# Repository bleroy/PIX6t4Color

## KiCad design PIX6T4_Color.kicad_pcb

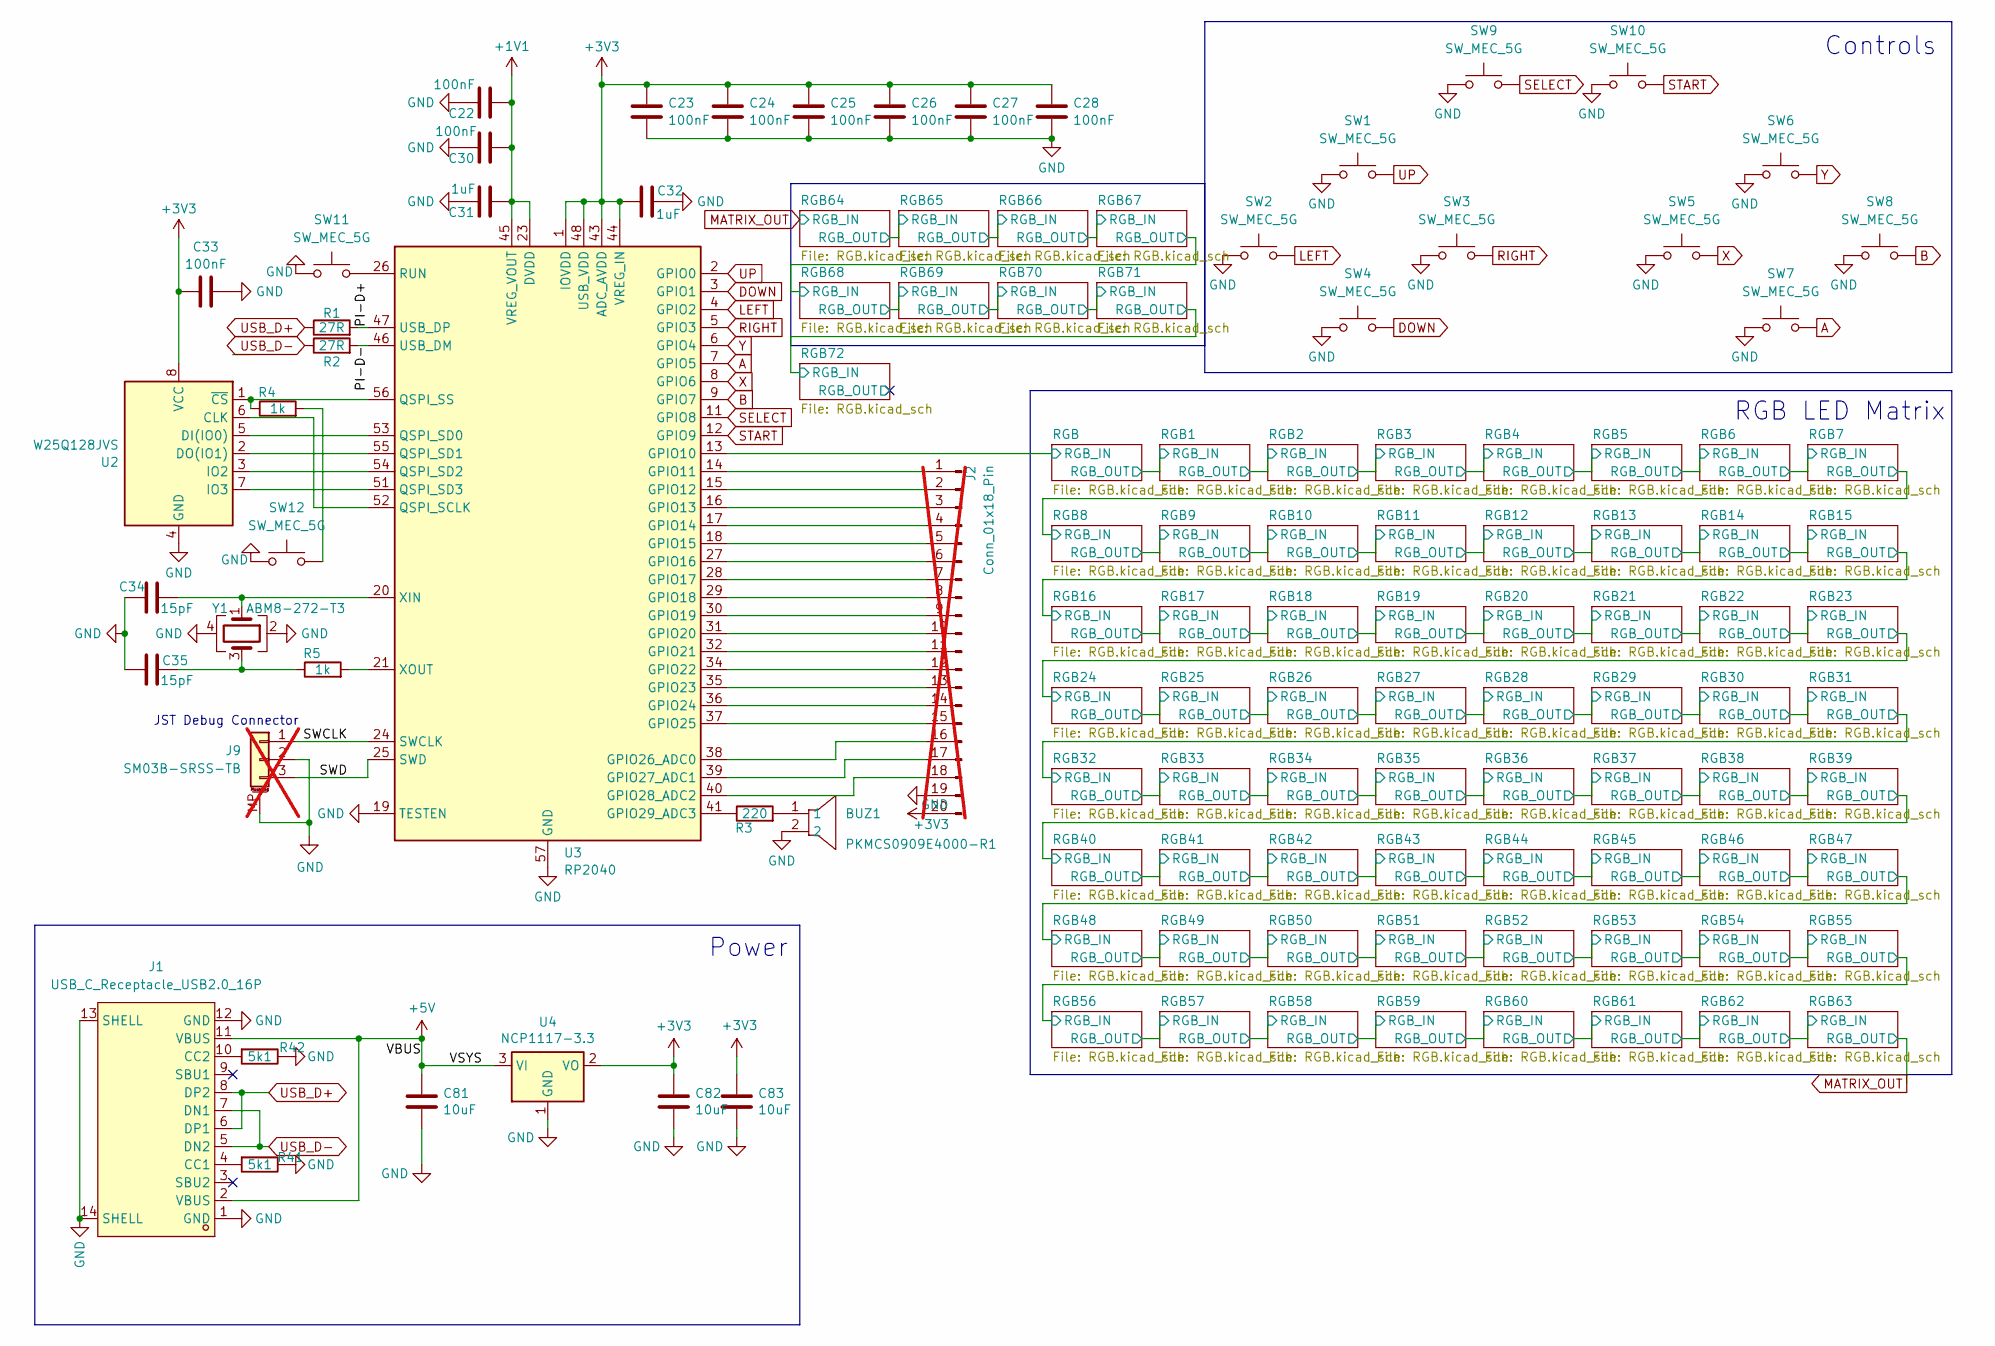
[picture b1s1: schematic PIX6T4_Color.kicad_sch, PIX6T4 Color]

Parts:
BUZ1: PKMCS0909E4000-R1; BUZ-SMD_L9.0-W9.0_PKMCS0909E4000-R1; JLCPCB Part # C910763
C22, C23, C24, C25, C26, C27, C28, C30, C33: 100nF; C_0402_1005Metric; JLCPCB Part # C1525
C31, C32: 1uF; C_0402_1005Metric; JLCPCB Part # C52923
C34, C35: 15pF; C_0402_1005Metric; JLCPCB Part # C1548
C81, C82, C83: 10uF; C_0402_1005Metric; JLCPCB Part # C15525
J1: USB_C_Receptacle_USB2.0_16P; USB-C-SMD_TYPE-C-6PIN-2MD-073; JLCPCB Part # C2765186
J2: Conn_01x18_Pin; PinHeader_1x20_P2.54mm_Vertical; not fitted
J9: SM03B-SRSS-TB; JST_SH_SM03B-SRSS-TB_1x03-1MP_P1.00mm_Horizontal; JLCPCB Part # C160389; not fitted
R1, R2: 27R; R_0805_2012Metric; JLCPCB Part # C17561
R3: 220; R_0402_1005Metric; JLCPCB Part # C25091
R4, R5: 1k; R_0402_1005Metric; JLCPCB Part # C11702
R41, R42: 5k1; R_0402_1005Metric; JLCPCB Part # C25905
SW1, SW2, SW3, SW4, SW5, SW6, SW7, SW8, SW9, SW10: SW_MEC_5G; SW-SMD_4P-L5.1-W5.1-P3.70-LS6.5-TL_H1.5; JLCPCB Part # C318884
SW11, SW12: SW_MEC_5G; SW-SMD_2P-TS24CA; JLCPCB Part # C393942
U2: W25Q128JVS; SOIC-8_L5.3-W5.3-P1.27-LS8.0-BL; JLCPCB Part # C97521
U3: RP2040; QFN-56-1EP_7x7mm_P0.4mm_EP3.2x3.2mm; JLCPCB Part # C2040
U4: NCP1117-3.3; SOT-223-3_TabPin2; JLCPCB Part # C6186
Y1: ABM8-272-T3; Oscillator_SMD_Abracon_ASE-4Pin_3.2x2.5mm; JLCPCB Part # C20625731

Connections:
+1V1: C22.1, C30.1, C31.1, U3.23 (DVDD), U3.45 (VREG_VOUT), U3.50 (DVDD)
+3V3: C23.1, C24.1, C25.1, C26.1, C27.1, C28.1, C32.1, C33.2, C82.1, C83.1, J2.20, U2.8 (VCC), U3.1 (IOVDD), U3.10 (IOVDD), U3.22 (IOVDD), U3.33 (IOVDD), U3.42 (IOVDD), U3.43 (ADC_AVDD), U3.44 (VREG_IN), U3.48 (USB_VDD), U3.49 (IOVDD), U4.2 (VO)
+5V: C81.1, J1.2 (VBUS), J1.11 (VBUS), U4.3 (VI); also elsewhere on the board
/PI-D+: R1.2, U3.47 (USB_DP)
/PI-D-: R2.2, U3.46 (USB_DM)
/RGB/RGB_IN: U3.13 (GPIO10); also elsewhere on the board
/SWCLK: J9.1, U3.24 (SWCLK)
/SWD: J9.3, U3.25 (SWD)
A: SW7.3 (B), SW7.4 (B), U3.7 (GPIO5)
B: SW8.3 (B), SW8.4 (B), U3.9 (GPIO7)
DOWN: SW4.3 (B), SW4.4 (B), U3.3 (GPIO1)
GND: BUZ1.2, C22.2, C23.2, C24.2, C25.2, C26.2, C27.2, C28.2, C30.2, C31.2, C32.2, C33.1, C34.1, C35.1, C81.2, C82.2, C83.2, J1.1 (GND), J1.12 (GND), J1.13 (SHELL), J1.14 (SHELL), J2.19, J9.2, J9.MP (MountPin), R41.1, R42.1, SW1.1 (A), SW1.2 (A), SW2.1 (A), SW2.2 (A), SW3.1 (A), SW3.2 (A), SW4.1 (A), SW4.2 (A), SW5.1 (A), SW5.2 (A), SW6.1 (A), SW6.2 (A), SW7.1 (A), SW7.2 (A), SW8.1 (A), SW8.2 (A), SW9.1 (A), SW9.2 (A), SW10.1 (A), SW10.2 (A), SW11.1 (A), SW11.2 (A), SW12.1 (A), SW12.2 (A), U2.4 (GND), U3.19 (TESTEN), U3.57 (GND), U4.1 (GND), Y1.2, Y1.4; also elsewhere on the board
LEFT: SW2.3 (B), SW2.4 (B), U3.4 (GPIO2)
unnamed: BUZ1.1, R3.2
unnamed: C35.2, R5.1, Y1.3
unnamed: J1.4 (CC1), R41.2
unnamed: J1.10 (CC2), R42.2
unnamed: J2.1, U3.14 (GPIO11)
unnamed: J2.2, U3.15 (GPIO12)
unnamed: J2.3, U3.16 (GPIO13)
unnamed: J2.4, U3.17 (GPIO14)
unnamed: J2.5, U3.18 (GPIO15)
unnamed: J2.6, U3.27 (GPIO16)
unnamed: J2.7, U3.28 (GPIO17)
unnamed: J2.8, U3.29 (GPIO18)
unnamed: J2.9, U3.30 (GPIO19)
unnamed: J2.10, U3.31 (GPIO20)
unnamed: J2.11, U3.32 (GPIO21)
unnamed: J2.12, U3.34 (GPIO22)
unnamed: J2.13, U3.35 (GPIO23)
unnamed: J2.14, U3.36 (GPIO24)
unnamed: J2.15, U3.37 (GPIO25)
unnamed: J2.16, U3.38 (GPIO26_ADC0)
unnamed: J2.17, U3.39 (GPIO27_ADC1)
unnamed: J2.18, U3.40 (GPIO28_ADC2)
unnamed: R4.2, SW12.3 (B), SW12.4 (B)
unnamed: U2.6 (CLK), U3.52 (QSPI_SCLK)
unnamed: U2.5 (DI(IO0)), U3.53 (QSPI_SD0)
unnamed: U2.2 (DO(IO1)), U3.55 (QSPI_SD1)
unnamed: U2.3 (IO2), U3.54 (QSPI_SD2)
unnamed: U2.7 (IO3), U3.51 (QSPI_SD3)
unnamed: R4.1, U2.1 (~CS), U3.56 (QSPI_SS)
unnamed: R3.1, U3.41 (GPIO29_ADC3)
unnamed: SW11.3 (B), SW11.4 (B), U3.26 (RUN)
unnamed: C34.2, U3.20 (XIN), Y1.1
unnamed: R5.2, U3.21 (XOUT)
RIGHT: SW3.3 (B), SW3.4 (B), U3.5 (GPIO3)
SELECT: SW9.3 (B), SW9.4 (B), U3.11 (GPIO8)
START: SW10.3 (B), SW10.4 (B), U3.12 (GPIO9)
UP: SW1.3 (B), SW1.4 (B), U3.2 (GPIO0)
USB_D+: J1.6 (DP1), J1.8 (DP2), R1.1
USB_D-: J1.5 (DN2), J1.7 (DN1), R2.1
X: SW5.3 (B), SW5.4 (B), U3.8 (GPIO6)
Y: SW6.3 (B), SW6.4 (B), U3.6 (GPIO4)

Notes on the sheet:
JST Debug Connector
Power
RGB LED Matrix
Controls

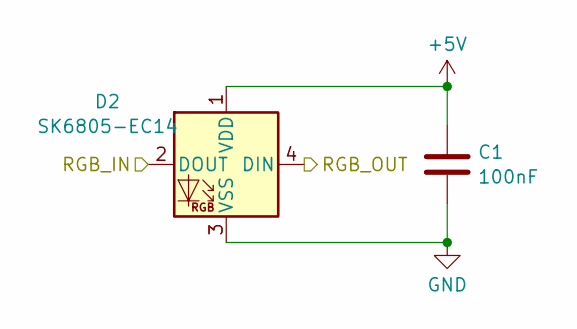
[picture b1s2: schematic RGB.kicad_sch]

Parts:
C1: 100nF; C_0402_1005Metric; JLCPCB Part # C1525
D2: SK6805-EC14; LED-SMD_4P-L1.4-W1.4-TL; JLCPCB Part # C2909055

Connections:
+5V: C1.1, D2.1 (VDD); also elsewhere on the board
/RGB/RGB_IN: D2.4 (DIN); also elsewhere on the board
/RGB/RGB_OUT: D2.2 (DOUT); also elsewhere on the board
GND: C1.2, D2.3 (VSS); also elsewhere on the board

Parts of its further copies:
C2, C3, C4, C5, C6, C7, C8, C9, C10, C11, C12, C13, C14, C15, C16, C17, C18, C19, C20, C21, C29, C36, C37, C38, C39, C40, C41, C42, C43, C44, C45, C46, C47, C48, C49, C50, C51, C52, C53, C54, C55, C56, C57, C58, C59, C60, C61, C62, C63, C64, C65, C66, C67, C68, C69, C70, C71, C72, C73, C74, C75, C76, C77, C78, C79, C80, C84, C85, C86, C87, C88, C89: 100nF; C_0402_1005Metric; JLCPCB Part # C1525
D1, D3, D4, D5, D6, D7, D8, D9, D10, D11, D12, D13, D14, D15, D16, D17, D18, D19, D20, D21, D22, D23, D24, D25, D26, D27, D28, D29, D30, D31, D32, D33, D34, D35, D36, D37, D38, D39, D40, D41, D42, D43, D44, D45, D46, D47, D48, D49, D50, D51, D52, D53, D54, D55, D56, D57, D58, D59, D60, D61, D62, D63, D64, D65, D66, D67, D68, D69, D70, D71, D72, D73: SK6805-EC14; LED-SMD_4P-L1.4-W1.4-TL; JLCPCB Part # C2909055

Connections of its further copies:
+5V: C2.1, C3.1, C4.1, C5.1, C6.1, C7.1, C8.1, C9.1, C10.1, C11.1, C12.1, C13.1, C14.1, C15.1, C16.1, C17.1, C18.1, C19.1, C20.1, C21.1, C29.1, C36.1, C37.1, C38.1, C39.1, C40.1, C41.1, C42.1, C43.1, C44.1, C45.1, C46.1, C47.1, C48.1, C49.1, C50.1, C51.1, C52.1, C53.1, C54.1, C55.1, C56.1, C57.1, C58.1, C59.1, C60.1, C61.1, C62.1, C63.1, C64.1, C65.1, C66.1, C67.1, C68.1, C69.1, C70.1, C71.1, C72.1, C73.1, C74.1, C75.1, C76.1, C77.1, C78.1, C79.1, C80.1, C84.1, C85.1, C86.1, C87.1, C88.1, C89.1, D1.1 (VDD), D3.1 (VDD), D4.1 (VDD), D5.1 (VDD), D6.1 (VDD), D7.1 (VDD), D8.1 (VDD), D9.1 (VDD), D10.1 (VDD), D11.1 (VDD), D12.1 (VDD), D13.1 (VDD), D14.1 (VDD), D15.1 (VDD), D16.1 (VDD), D17.1 (VDD), D18.1 (VDD), D19.1 (VDD), D20.1 (VDD), D21.1 (VDD), D22.1 (VDD), D23.1 (VDD), D24.1 (VDD), D25.1 (VDD), D26.1 (VDD), D27.1 (VDD), D28.1 (VDD), D29.1 (VDD), D30.1 (VDD), D31.1 (VDD), D32.1 (VDD), D33.1 (VDD), D34.1 (VDD), D35.1 (VDD), D36.1 (VDD), D37.1 (VDD), D38.1 (VDD), D39.1 (VDD), D40.1 (VDD), D41.1 (VDD), D42.1 (VDD), D43.1 (VDD), D44.1 (VDD), D45.1 (VDD), D46.1 (VDD), D47.1 (VDD), D48.1 (VDD), D49.1 (VDD), D50.1 (VDD), D51.1 (VDD), D52.1 (VDD), D53.1 (VDD), D54.1 (VDD), D55.1 (VDD), D56.1 (VDD), D57.1 (VDD), D58.1 (VDD), D59.1 (VDD), D60.1 (VDD), D61.1 (VDD), D62.1 (VDD), D63.1 (VDD), D64.1 (VDD), D65.1 (VDD), D66.1 (VDD), D67.1 (VDD), D68.1 (VDD), D69.1 (VDD), D70.1 (VDD), D71.1 (VDD), D72.1 (VDD), D73.1 (VDD); also elsewhere on the board
/RGB1/RGB_OUT: D1.2 (DOUT), D3.4 (DIN)
/RGB2/RGB_OUT: D3.2 (DOUT), D4.4 (DIN)
/RGB3/RGB_OUT: D4.2 (DOUT), D5.4 (DIN)
/RGB4/RGB_OUT: D5.2 (DOUT), D6.4 (DIN)
/RGB5/RGB_OUT: D6.2 (DOUT), D7.4 (DIN)
/RGB6/RGB_OUT: D7.2 (DOUT), D8.4 (DIN)
/RGB7/RGB_OUT: D8.2 (DOUT), D9.4 (DIN)
/RGB8/RGB_OUT: D9.2 (DOUT), D10.4 (DIN)
/RGB10/RGB_IN: D10.2 (DOUT), D11.4 (DIN)
/RGB10/RGB_OUT: D11.2 (DOUT), D12.4 (DIN)
/RGB11/RGB_OUT: D12.2 (DOUT), D13.4 (DIN)
/RGB12/RGB_OUT: D13.2 (DOUT), D14.4 (DIN)
/RGB13/RGB_OUT: D14.2 (DOUT), D15.4 (DIN)
/RGB14/RGB_OUT: D15.2 (DOUT), D16.4 (DIN)
/RGB15/RGB_OUT: D16.2 (DOUT), D17.4 (DIN)
/RGB16/RGB_OUT: D17.2 (DOUT), D18.4 (DIN)
/RGB17/RGB_OUT: D18.2 (DOUT), D19.4 (DIN)
/RGB18/RGB_OUT: D19.2 (DOUT), D20.4 (DIN)
/RGB19/RGB_OUT: D20.2 (DOUT), D21.4 (DIN)
/RGB20/RGB_OUT: D21.2 (DOUT), D22.4 (DIN)
/RGB21/RGB_OUT: D22.2 (DOUT), D23.4 (DIN)
/RGB22/RGB_OUT: D23.2 (DOUT), D24.4 (DIN)
/RGB23/RGB_OUT: D24.2 (DOUT), D25.4 (DIN)
/RGB24/RGB_OUT: D25.2 (DOUT), D26.4 (DIN)
/RGB25/RGB_OUT: D26.2 (DOUT), D27.4 (DIN)
/RGB26/RGB_OUT: D27.2 (DOUT), D28.4 (DIN)
/RGB27/RGB_OUT: D28.2 (DOUT), D29.4 (DIN)
/RGB28/RGB_OUT: D29.2 (DOUT), D30.4 (DIN)
/RGB29/RGB_OUT: D30.2 (DOUT), D31.4 (DIN)
/RGB30/RGB_OUT: D31.2 (DOUT), D32.4 (DIN)
/RGB31/RGB_OUT: D32.2 (DOUT), D33.4 (DIN)
/RGB32/RGB_OUT: D33.2 (DOUT), D34.4 (DIN)
/RGB33/RGB_OUT: D34.2 (DOUT), D35.4 (DIN)
/RGB34/RGB_OUT: D35.2 (DOUT), D36.4 (DIN)
/RGB35/RGB_OUT: D36.2 (DOUT), D37.4 (DIN)
/RGB36/RGB_OUT: D37.2 (DOUT), D38.4 (DIN)
/RGB37/RGB_OUT: D38.2 (DOUT), D39.4 (DIN)
/RGB38/RGB_OUT: D39.2 (DOUT), D40.4 (DIN)
/RGB39/RGB_OUT: D40.2 (DOUT), D41.4 (DIN)
/RGB40/RGB_OUT: D41.2 (DOUT), D42.4 (DIN)
/RGB41/RGB_OUT: D42.2 (DOUT), D43.4 (DIN)
/RGB42/RGB_OUT: D43.2 (DOUT), D44.4 (DIN)
/RGB43/RGB_OUT: D44.2 (DOUT), D45.4 (DIN)
/RGB44/RGB_OUT: D45.2 (DOUT), D46.4 (DIN)
/RGB45/RGB_OUT: D46.2 (DOUT), D47.4 (DIN)
/RGB46/RGB_OUT: D47.2 (DOUT), D48.4 (DIN)
/RGB47/RGB_OUT: D48.2 (DOUT), D49.4 (DIN)
/RGB48/RGB_OUT: D49.2 (DOUT), D50.4 (DIN)
/RGB49/RGB_OUT: D50.2 (DOUT), D51.4 (DIN)
/RGB50/RGB_OUT: D51.2 (DOUT), D52.4 (DIN)
/RGB51/RGB_OUT: D52.2 (DOUT), D53.4 (DIN)
/RGB52/RGB_OUT: D53.2 (DOUT), D54.4 (DIN)
/RGB53/RGB_OUT: D54.2 (DOUT), D55.4 (DIN)
/RGB54/RGB_OUT: D55.2 (DOUT), D56.4 (DIN)
/RGB55/RGB_OUT: D56.2 (DOUT), D57.4 (DIN)
/RGB56/RGB_OUT: D57.2 (DOUT), D58.4 (DIN)
/RGB57/RGB_OUT: D58.2 (DOUT), D59.4 (DIN)
/RGB58/RGB_OUT: D59.2 (DOUT), D60.4 (DIN)
/RGB59/RGB_OUT: D60.2 (DOUT), D61.4 (DIN)
/RGB60/RGB_OUT: D61.2 (DOUT), D62.4 (DIN)
/RGB61/RGB_OUT: D62.2 (DOUT), D63.4 (DIN)
/RGB62/RGB_OUT: D63.2 (DOUT), D64.4 (DIN)
/RGB64/RGB_OUT: D65.2 (DOUT), D66.4 (DIN)
/RGB65/RGB_OUT: D66.2 (DOUT), D67.4 (DIN)
/RGB66/RGB_OUT: D67.2 (DOUT), D68.4 (DIN)
/RGB67/RGB_OUT: D68.2 (DOUT), D69.4 (DIN)
/RGB68/RGB_OUT: D69.2 (DOUT), D70.4 (DIN)
/RGB69/RGB_OUT: D70.2 (DOUT), D71.4 (DIN)
/RGB70/RGB_OUT: D71.2 (DOUT), D72.4 (DIN)
/RGB71/RGB_OUT: D72.2 (DOUT), D73.4 (DIN)
/RGB72/RGB_OUT: D73.2 (DOUT)
/RGB/RGB_OUT: D1.4 (DIN); also elsewhere on the board
GND: C2.2, C3.2, C4.2, C5.2, C6.2, C7.2, C8.2, C9.2, C10.2, C11.2, C12.2, C13.2, C14.2, C15.2, C16.2, C17.2, C18.2, C19.2, C20.2, C21.2, C29.2, C36.2, C37.2, C38.2, C39.2, C40.2, C41.2, C42.2, C43.2, C44.2, C45.2, C46.2, C47.2, C48.2, C49.2, C50.2, C51.2, C52.2, C53.2, C54.2, C55.2, C56.2, C57.2, C58.2, C59.2, C60.2, C61.2, C62.2, C63.2, C64.2, C65.2, C66.2, C67.2, C68.2, C69.2, C70.2, C71.2, C72.2, C73.2, C74.2, C75.2, C76.2, C77.2, C78.2, C79.2, C80.2, C84.2, C85.2, C86.2, C87.2, C88.2, C89.2, D1.3 (VSS), D3.3 (VSS), D4.3 (VSS), D5.3 (VSS), D6.3 (VSS), D7.3 (VSS), D8.3 (VSS), D9.3 (VSS), D10.3 (VSS), D11.3 (VSS), D12.3 (VSS), D13.3 (VSS), D14.3 (VSS), D15.3 (VSS), D16.3 (VSS), D17.3 (VSS), D18.3 (VSS), D19.3 (VSS), D20.3 (VSS), D21.3 (VSS), D22.3 (VSS), D23.3 (VSS), D24.3 (VSS), D25.3 (VSS), D26.3 (VSS), D27.3 (VSS), D28.3 (VSS), D29.3 (VSS), D30.3 (VSS), D31.3 (VSS), D32.3 (VSS), D33.3 (VSS), D34.3 (VSS), D35.3 (VSS), D36.3 (VSS), D37.3 (VSS), D38.3 (VSS), D39.3 (VSS), D40.3 (VSS), D41.3 (VSS), D42.3 (VSS), D43.3 (VSS), D44.3 (VSS), D45.3 (VSS), D46.3 (VSS), D47.3 (VSS), D48.3 (VSS), D49.3 (VSS), D50.3 (VSS), D51.3 (VSS), D52.3 (VSS), D53.3 (VSS), D54.3 (VSS), D55.3 (VSS), D56.3 (VSS), D57.3 (VSS), D58.3 (VSS), D59.3 (VSS), D60.3 (VSS), D61.3 (VSS), D62.3 (VSS), D63.3 (VSS), D64.3 (VSS), D65.3 (VSS), D66.3 (VSS), D67.3 (VSS), D68.3 (VSS), D69.3 (VSS), D70.3 (VSS), D71.3 (VSS), D72.3 (VSS), D73.3 (VSS); also elsewhere on the board
MATRIX_OUT: D64.2 (DOUT), D65.4 (DIN)

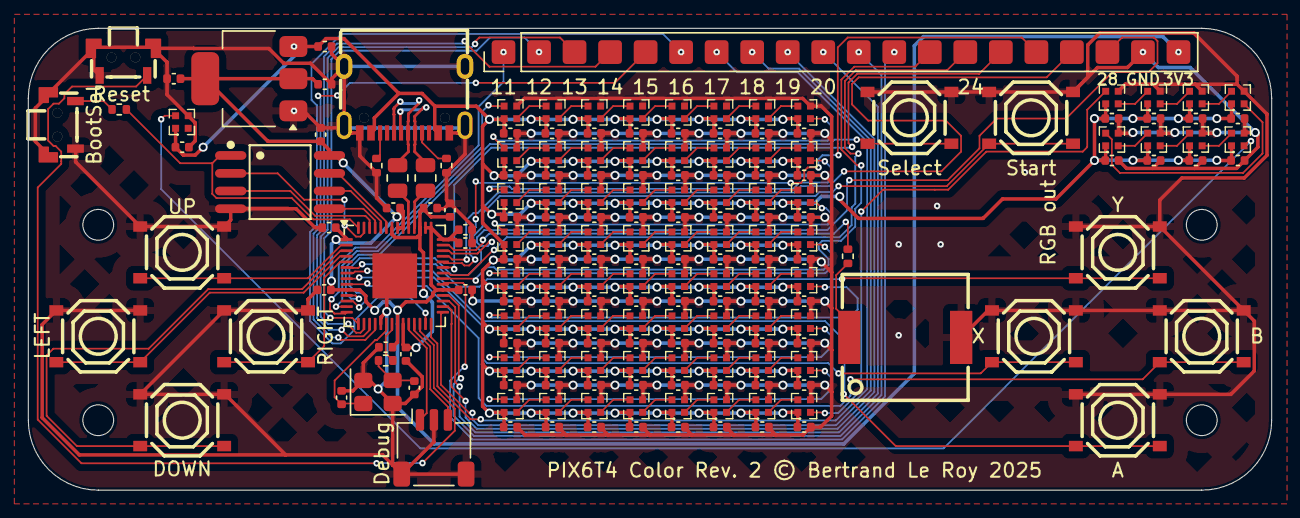
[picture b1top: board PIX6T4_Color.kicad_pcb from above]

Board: 2 copper layers, 88.9 x 33.0 mm, 189 parts (0 on the bottom side), 126 nets.

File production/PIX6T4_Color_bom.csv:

Designator,Footprint,Quantity,Value,LCSC Part #
BUZ1,BUZ-SMD_L9.0-W9.0_PKMCS0909E4000-R1,1,PKMCS0909E4000-R1,
"C1, C10, C11, C12, C13, C14, C15, C16, C17, C18, C19, C2, C22, C23, C24, C25, C26, C27, C28, C3, C30, C33, C36, C37, C38, C39, C4, C40, C41, C42, C43, C44, C45, C46, C47, C48, C49, C5, C50, C51, C52, C53, C54, C55, C56, C57, C58, C59, C6, C60, C61, C62, C63, C64, C65, C66, C67, C68, C69, C7, C70, C71, C72, C73, C74, C75, C76, C77, C78, C79, C8, C80, C9",0402,73,100nF,C1525
"C31, C32",0402,2,1uF,C52923
"C34, C35",0402,2,15pF,C1548
"C81, C82, C83",0402,3,10uF,C15525
"D1, D10, D11, D12, D13, D14, D15, D16, D17, D18, D19, D2, D20, D21, D22, D23, D24, D25, D26, D27, D28, D29, D3, D30, D31, D32, D33, D34, D35, D36, D37, D38, D39, D4, D40, D41, D42, D43, D44, D45, D46, D47, D48, D49, D5, D50, D51, D52, D53, D54, D55, D56, D57, D58, D59, D6, D60, D61, D62, D63, D64, D7, D8, D9",LED-SMD_4P-L1.4-W1.4-TL,64,SK6805-EC14,C2909055
J1,USB-C-SMD_TYPE-C-6PIN-2MD-073,1,USB_C_Receptacle_USB2.0_16P,C2765186
"R1, R2",0805,2,27R,C17561
R3,0402,1,220,C25091
"R4, R5",0402,2,1k,C11702
"R41, R42",0402,2,5k1,C25905
"SW1, SW10, SW2, SW3, SW4, SW5, SW6, SW7, SW8, SW9",SW-SMD_4P-L5.1-W5.1-P3.70-LS6.5-TL_H1.5,10,SW_MEC_5G,C318884
"SW11, SW12",SW-SMD_TS24CA,2,SW_MEC_5G,C393942
U2,SOIC-8_L5.3-W5.3-P1.27-LS8.0-BL,1,W25Q128JVS,C97521
U3,QFN-56-1EP_7x7mm_P0.4mm_EP3.2x3.2mm,1,RP2040,C2040
U4,SOT-223-3_TabPin2,1,NCP1117-3.3,C6186
Y1,Oscillator_SMD_Abracon_ASE-4Pin_3.2x2.5mm,1,ABM8-272-T3,C20625731

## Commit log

2025-07-26 Initial population
2025-07-29 Start implementing MsPixMan
2025-07-29 Add implementation for the real hardware
    Downgrade Python to 3.4
2025-08-02 Rev. 2
2025-08-03 MsPixMan rendering and player movement implemented
2025-08-03 Fix boundary condition for labyrinth topology
2025-08-22 Small fixes to the printed parts
2025-09-11 Add power / invader logo light
2025-09-11 Power LED window
    PCB holders around the device
2025-09-15 Smol sings

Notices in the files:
PIX6T4_Color.kicad_pcb:
PIX6T4 Color Rev. 2 © Bertrand Le Roy 2025
